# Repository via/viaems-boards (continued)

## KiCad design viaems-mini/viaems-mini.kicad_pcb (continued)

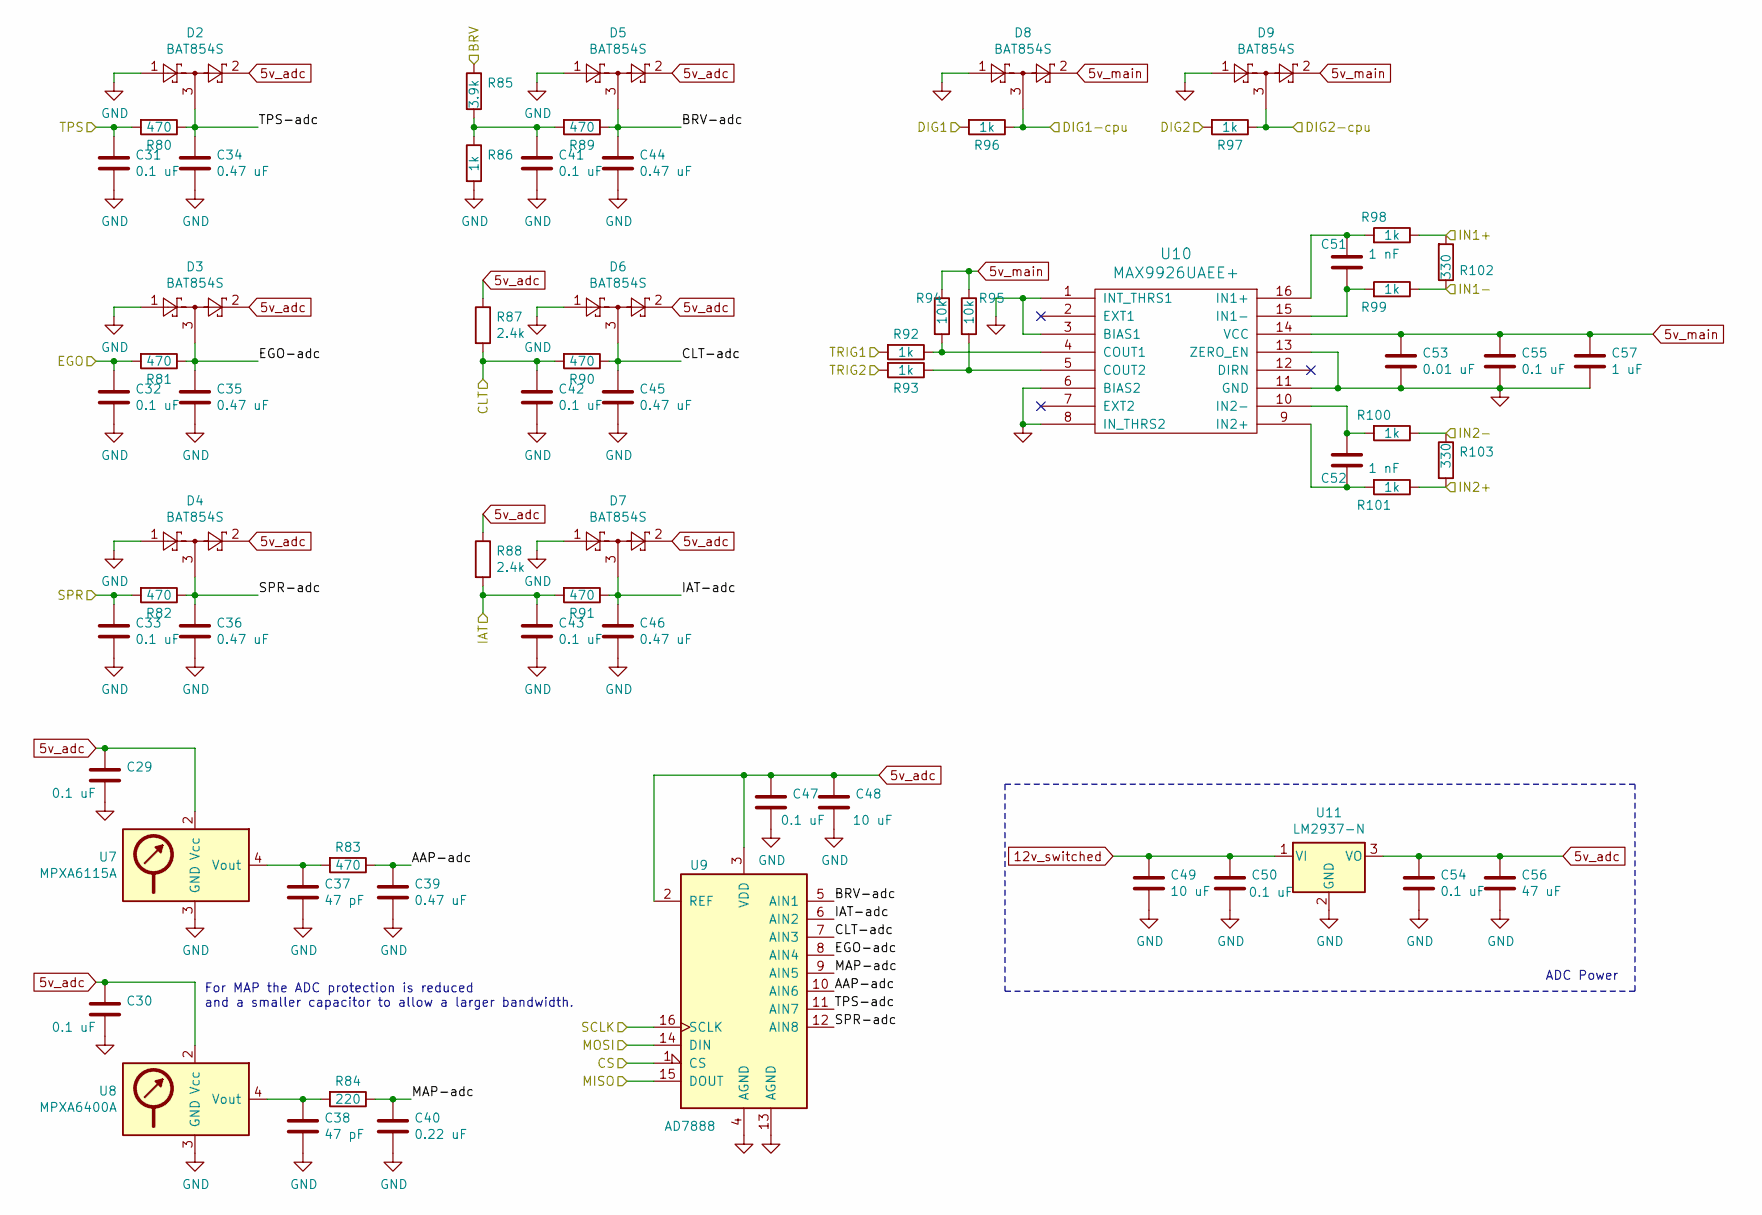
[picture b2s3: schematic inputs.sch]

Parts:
C29, C30, C31, C32, C33, C41, C42, C43, C47, C50, C54, C55: 0.1 uF; C_0805_2012Metric
C34, C35, C36, C39, C44, C45, C46: 0.47 uF; C_0805_2012Metric
C37, C38: 47 pF; C_0805_2012Metric
C40: 0.22 uF; C_0805_2012Metric
C48, C49: 10 uF; C_0805_2012Metric
C51, C52: 1 nF; C_0805_2012Metric
C53: 0.01 uF; C_0805_2012Metric
C56: 47 uF; C_1206_3216Metric; Digikey-Part 478-9009-1-ND
C57: 1 uF; C_0805_2012Metric
D2, D3, D4, D5, D6, D7, D8, D9: BAT854S; SOT-23
R80, R81, R82, R83, R89, R90, R91: 470; R_0805_2012Metric
R84: 220; R_0805_2012Metric
R85: 3.9k; R_0805_2012Metric
R86, R92, R93, R96, R97, R98, R99, R100, R101: 1k; R_0805_2012Metric
R87, R88: 2.4k; R_0805_2012Metric
R94, R95: 10k; R_0805_2012Metric
R102, R103: 330; R_Axial_DIN0204_L3.6mm_D1.6mm_P2.54mm_Vertical
U7: MPXA6115A; Freescale_98ARH99089A
U8: MPXA6400A; Freescale_98ARH99089A
U9: AD7888; SOIC-16_3.9x9.9mm_P1.27mm
U10: MAX9926UAEE+; QSOP-16_3.9x4.9mm_P0.635mm
U11: LM2937-N; TO-263-3_TabPin2

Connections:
5v_adc: C29.1, C30.1, C47.1, C48.1, C54.1, C56.1, D2.2, D3.2, D4.2, D5.2, D6.2, D7.2, R87.1, R88.1, U7.2 (Vcc), U8.2 (Vcc), U9.2 (REF), U9.3 (VDD), U11.3 (VO); also elsewhere on the board
5v_main: C53.1, C55.1, C57.1, D8.2, D9.2, R94.1, R95.1, U10.14 (VCC); also elsewhere on the board
12v_switched: C49.1, C50.1, U11.1 (VI); also elsewhere on the board
/BRV: R85.1; also elsewhere on the board
/CLT: C42.1, R87.2, R90.2; also elsewhere on the board
/DIG1: R96.2; also elsewhere on the board
/DIG2: R97.2; also elsewhere on the board
/EGO: C32.1, R81.2; also elsewhere on the board
/IAT: C43.1, R88.2, R91.2; also elsewhere on the board
/IN1+: R98.1, R102.2; also elsewhere on the board
/IN1-: R99.1, R102.1; also elsewhere on the board
/IN2+: R101.1, R103.2; also elsewhere on the board
/IN2-: R100.1, R103.1; also elsewhere on the board
/Inputs/AAP-adc: C39.1, R83.1, U9.10 (AIN6)
/Inputs/BRV-adc: C44.1, D5.3, R89.1, U9.5 (AIN1)
/Inputs/CLT-adc: C45.1, D6.3, R90.1, U9.7 (AIN3)
/Inputs/CS: U9.1 (CS); also elsewhere on the board
/Inputs/DIG1-cpu: D8.3, R96.1; also elsewhere on the board
/Inputs/DIG2-cpu: D9.3, R97.1; also elsewhere on the board
/Inputs/EGO-adc: C35.1, D3.3, R81.1, U9.8 (AIN4)
/Inputs/IAT-adc: C46.1, D7.3, R91.1, U9.6 (AIN2)
/Inputs/MAP-adc: C40.1, R84.1, U9.9 (AIN5)
/Inputs/MISO: U9.15 (DOUT); also elsewhere on the board
/Inputs/MOSI: U9.14 (DIN); also elsewhere on the board
/Inputs/SCLK: U9.16 (SCLK); also elsewhere on the board
/Inputs/SPR-adc: C36.1, D4.3, R82.1, U9.12 (AIN8)
/Inputs/TPS-adc: C34.1, D2.3, R80.1, U9.11 (AIN7)
/Inputs/TRIG1: R92.2; also elsewhere on the board
/Inputs/TRIG2: R93.2; also elsewhere on the board
/SPR: C33.1, R82.2; also elsewhere on the board
/TPS: C31.1, R80.2; also elsewhere on the board
GND: C29.2, C30.2, C31.2, C32.2, C33.2, C34.2, C35.2, C36.2, C37.2, C38.2, C39.2, C40.2, C41.2, C42.2, C43.2, C44.2, C45.2, C46.2, C47.2, C48.2, C49.2, C50.2, C53.2, C54.2, C55.2, C56.2, C57.2, D2.1, D3.1, D4.1, D5.1, D6.1, D7.1, D8.1, D9.1, R86.2, U7.3 (GND), U8.3 (GND), U9.4 (AGND), U9.13 (AGND), U10.1 (INT_THRS1), U10.3 (BIAS1), U10.6 (BIAS2), U10.8 (IN_THRS2), U10.11 (GND), U10.13 (ZERO_EN), U11.2 (GND); also elsewhere on the board
unnamed: C37.1, R83.2, U7.4 (Vout)
unnamed: C38.1, R84.2, U8.4 (Vout)
unnamed: C41.1, R85.2, R86.1, R89.2
unnamed: C51.1, R99.2, U10.15 (IN1-)
unnamed: C51.2, R98.2, U10.16 (IN1+)
unnamed: C52.1, R100.2, U10.10 (IN2-)
unnamed: C52.2, R101.2, U10.9 (IN2+)
unnamed: R92.1, R94.2, U10.4 (COUT1)
unnamed: R93.1, R95.2, U10.5 (COUT2)

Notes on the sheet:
For MAP the ADC protection is reduced and a smaller capacitor to allow a larger bandwidth.
ADC Power

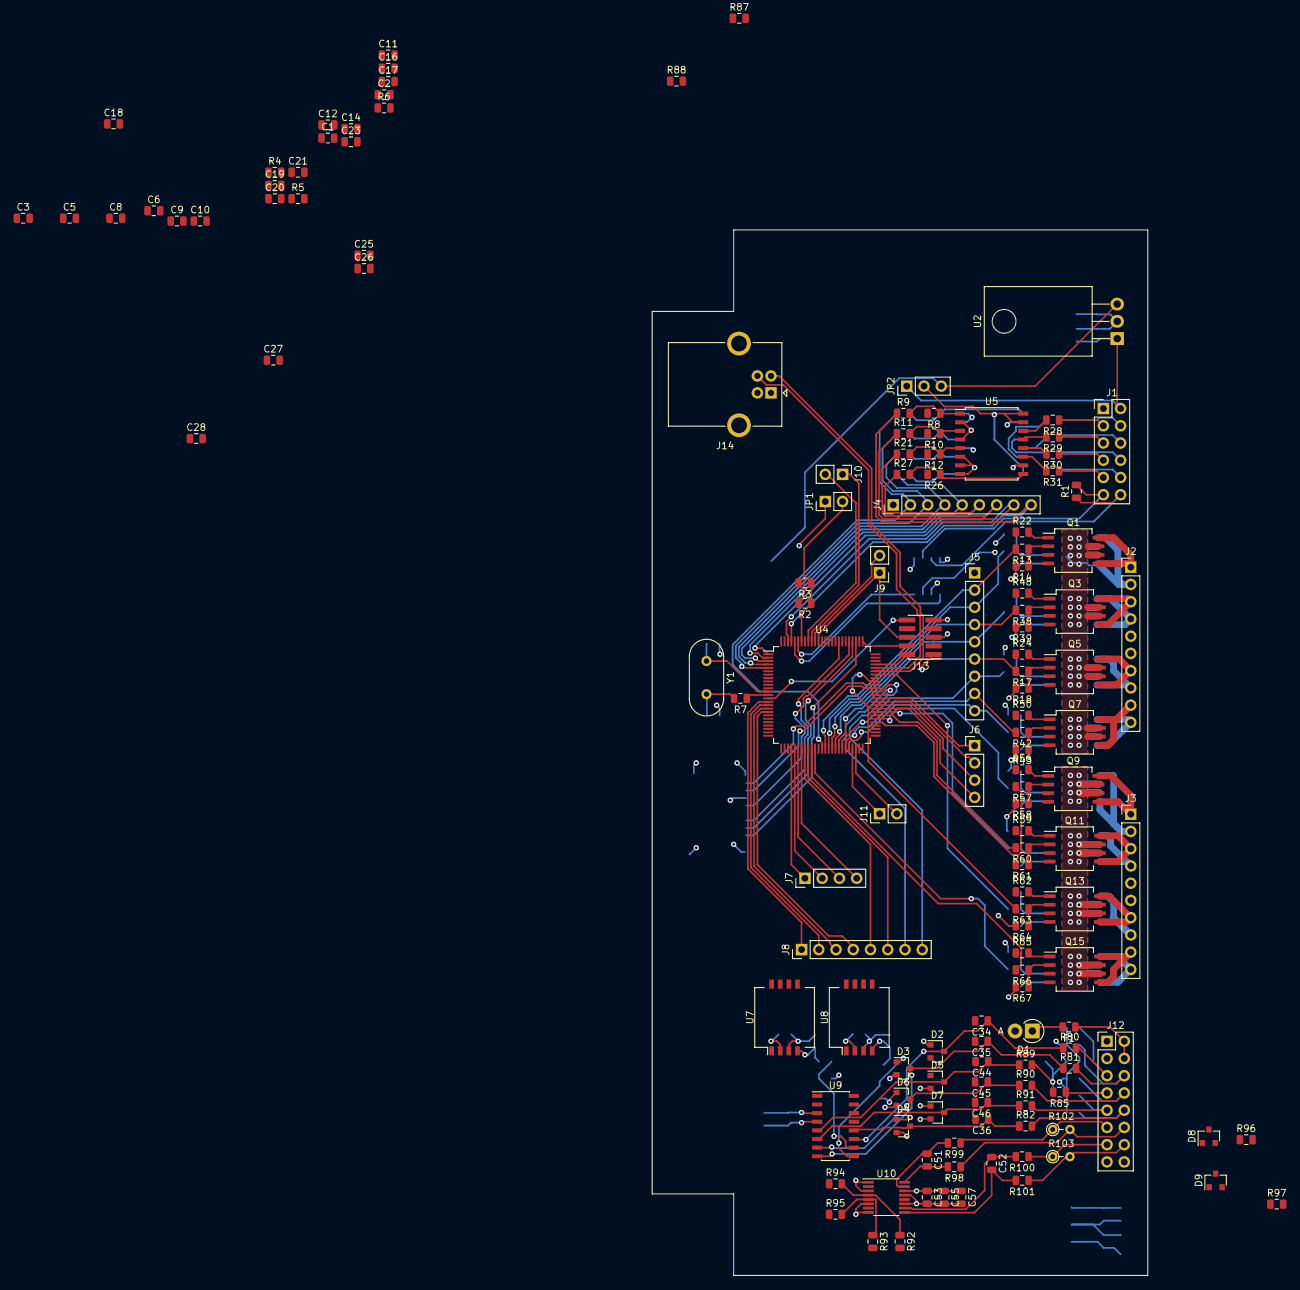
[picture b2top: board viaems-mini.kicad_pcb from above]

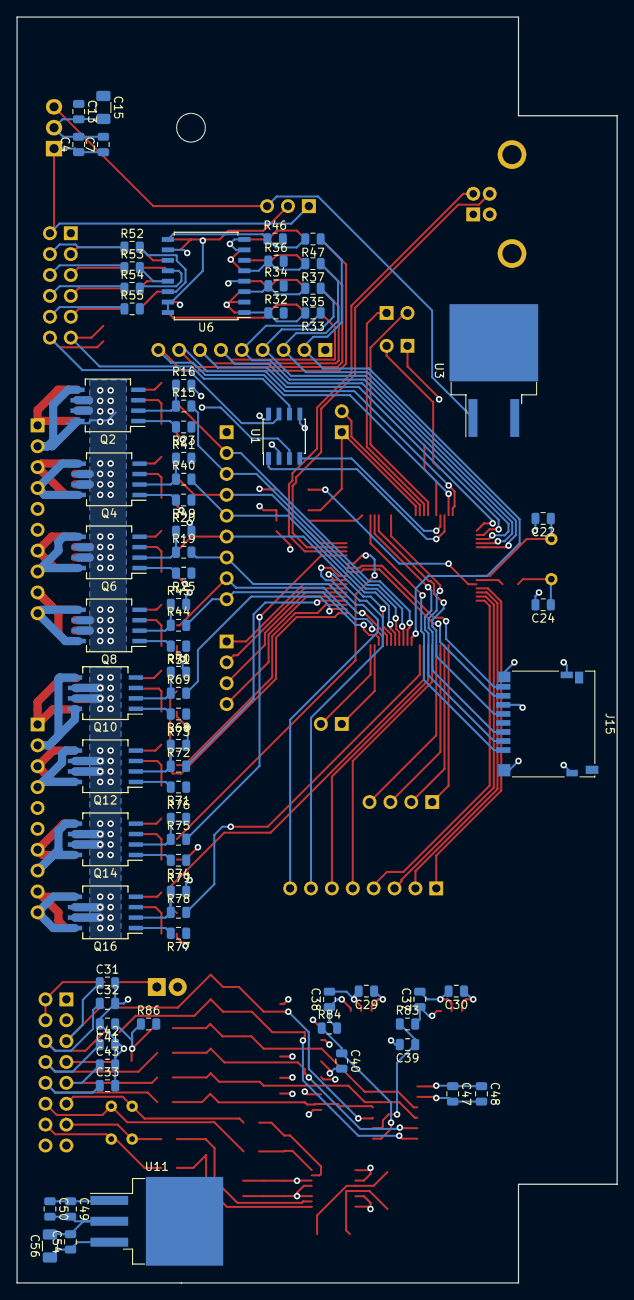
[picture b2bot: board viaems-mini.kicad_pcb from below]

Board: 4 copper layers, 73.0 x 154.0 mm, 215 parts (76 on the bottom side), 189 nets.
